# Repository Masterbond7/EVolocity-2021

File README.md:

# EVolocity-2021 Cart Repository

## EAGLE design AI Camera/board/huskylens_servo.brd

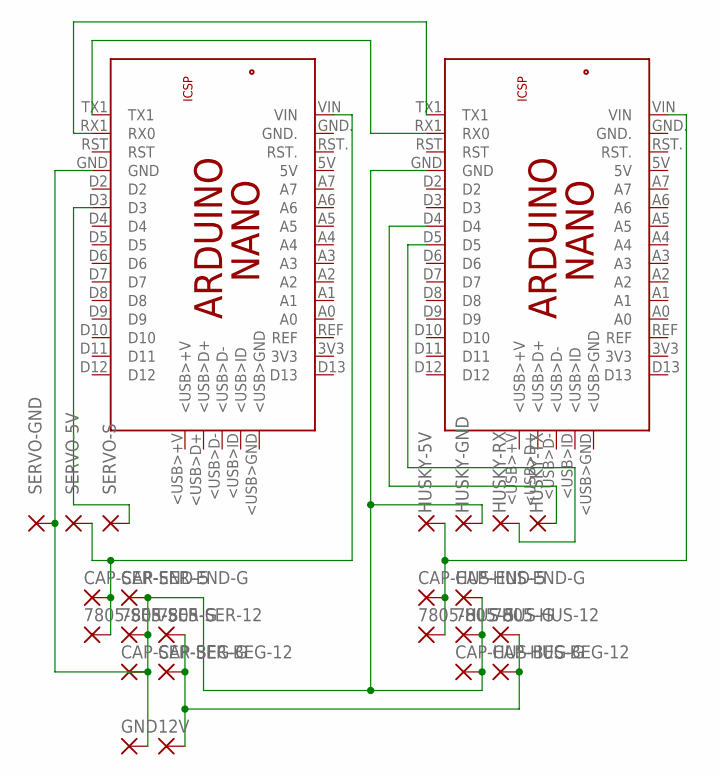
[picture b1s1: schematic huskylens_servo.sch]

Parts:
12V, 7805-HUS-5, 7805-HUS-12, 7805-HUS-G, 7805-SER-5, 7805-SER-12, 7805-SER-G: 2,15/1,0
CAP-HUS-BEG-12: 2,15/1,0
CAP-HUS-BEG-G: 2,15/1,0
CAP-HUS-END-5: 2,15/1,0
CAP-HUS-END-G: 2,15/1,0
CAP-SER-BEG-12: 2,15/1,0
CAP-SER-BEG-G: 2,15/1,0
CAP-SER-END-5: 2,15/1,0
CAP-SER-END-G: 2,15/1,0
GND: 2,15/1,0
HUSKY-5V: 2,15/1,0
HUSKY-ARD: ARDUINO_NANO
HUSKY-GND: 2,15/1,0
HUSKY-RX: 2,15/1,0
HUSKY-TX: 2,15/1,0
SERVO-5V: 2,15/1,0
SERVO-ARD: ARDUINO_NANO
SERVO-GND: 2,15/1,0
SERVO-S: 2,15/1,0

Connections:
unnamed: HUSKY-ARD.RX1 (RX0), SERVO-ARD.TX1
unnamed: HUSKY-ARD.TX1, SERVO-ARD.RX1 (RX0)
unnamed: 7805-HUS-G.1, 7805-SER-G.1, CAP-HUS-BEG-G.1, CAP-HUS-END-G.1, CAP-SER-BEG-G.1, CAP-SER-END-G.1, GND.1, HUSKY-ARD.GND, HUSKY-GND.1, SERVO-ARD.GND, SERVO-GND.1
unnamed: HUSKY-ARD.D5, HUSKY-RX.1
unnamed: SERVO-ARD.D3, SERVO-S.1
unnamed: 12V.1, 7805-HUS-12.1, 7805-SER-12.1, CAP-HUS-BEG-12.1, CAP-SER-BEG-12.1
unnamed: 7805-HUS-5.1, CAP-HUS-END-5.1, HUSKY-5V.1, HUSKY-ARD.VIN
unnamed: 7805-SER-5.1, CAP-SER-END-5.1, SERVO-5V.1, SERVO-ARD.VIN
unnamed: HUSKY-ARD.D4, HUSKY-TX.1

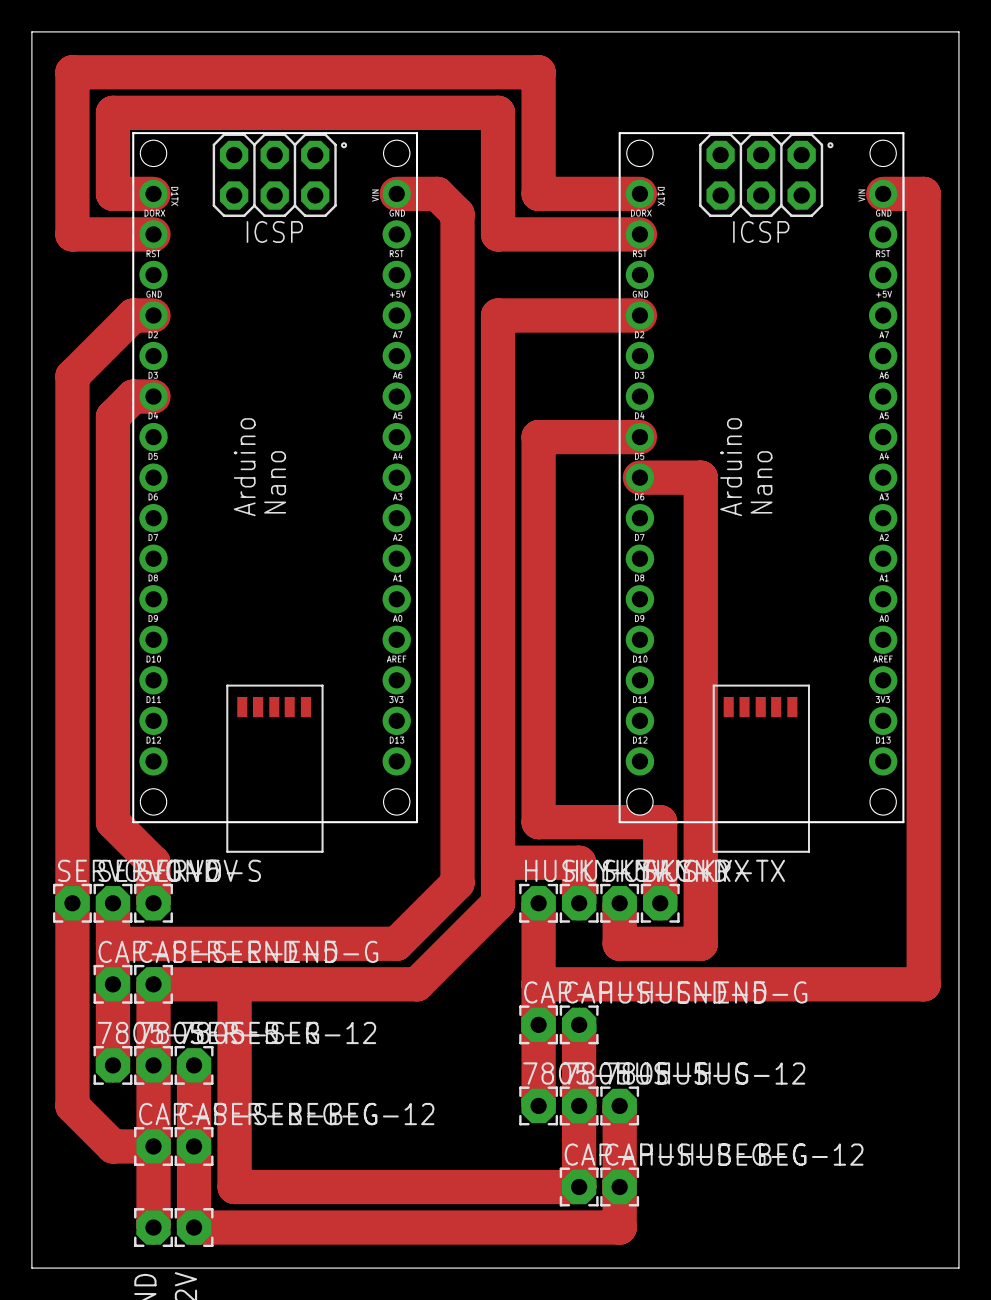
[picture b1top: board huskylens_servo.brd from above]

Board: 2 copper layers, 58.0 x 77.3 mm, 25 parts (0 on the bottom side), 9 nets.

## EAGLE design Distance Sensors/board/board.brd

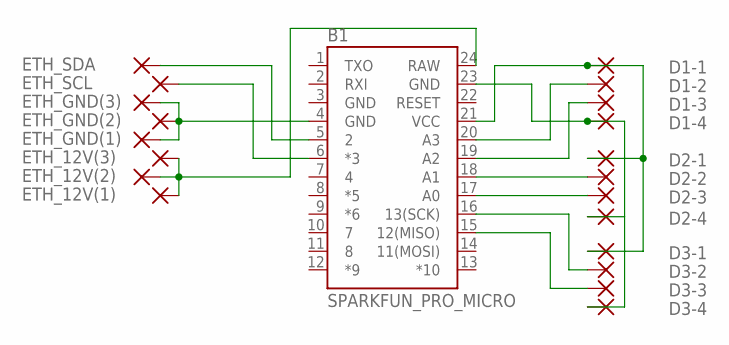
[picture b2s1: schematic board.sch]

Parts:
B1: SPARKFUN_PRO_MICRO
D1-1, D1-2, D1-3, D1-4, D2-1, D2-2, D2-3, D2-4, D3-1, D3-2, D3-3, D3-4: 2,15/1,0
ETH_12V(1), ETH_12V(2), ETH_12V(3): 2,15/1,0
ETH_GND(1), ETH_GND(2), ETH_GND(3): 2,15/1,0
ETH_SCL: 2,15/1,0
ETH_SDA: 2,15/1,0

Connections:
GND: B1.3 (GND)
unnamed: B1.4 (GND), ETH_GND(1).1, ETH_GND(2).1, ETH_GND(3).1
unnamed: B1.23 (GND), D1-4.1, D2-4.1, D3-4.1
unnamed: B1.21 (VCC), D1-1.1, D2-1.1, D3-1.1
unnamed: B1.19 (A2), D1-3.1
unnamed: B1.20 (A3), D1-2.1
unnamed: B1.18 (A1), D2-2.1
unnamed: B1.17 (A0), D2-3.1
unnamed: B1.16 (13(SCK)), D3-2.1
unnamed: B1.15 (12(MISO)), D3-3.1
unnamed: B1.24 (RAW), ETH_12V(1).1, ETH_12V(2).1, ETH_12V(3).1
unnamed: B1.5 (2), ETH_SDA.1
unnamed: B1.6 (*3), ETH_SCL.1

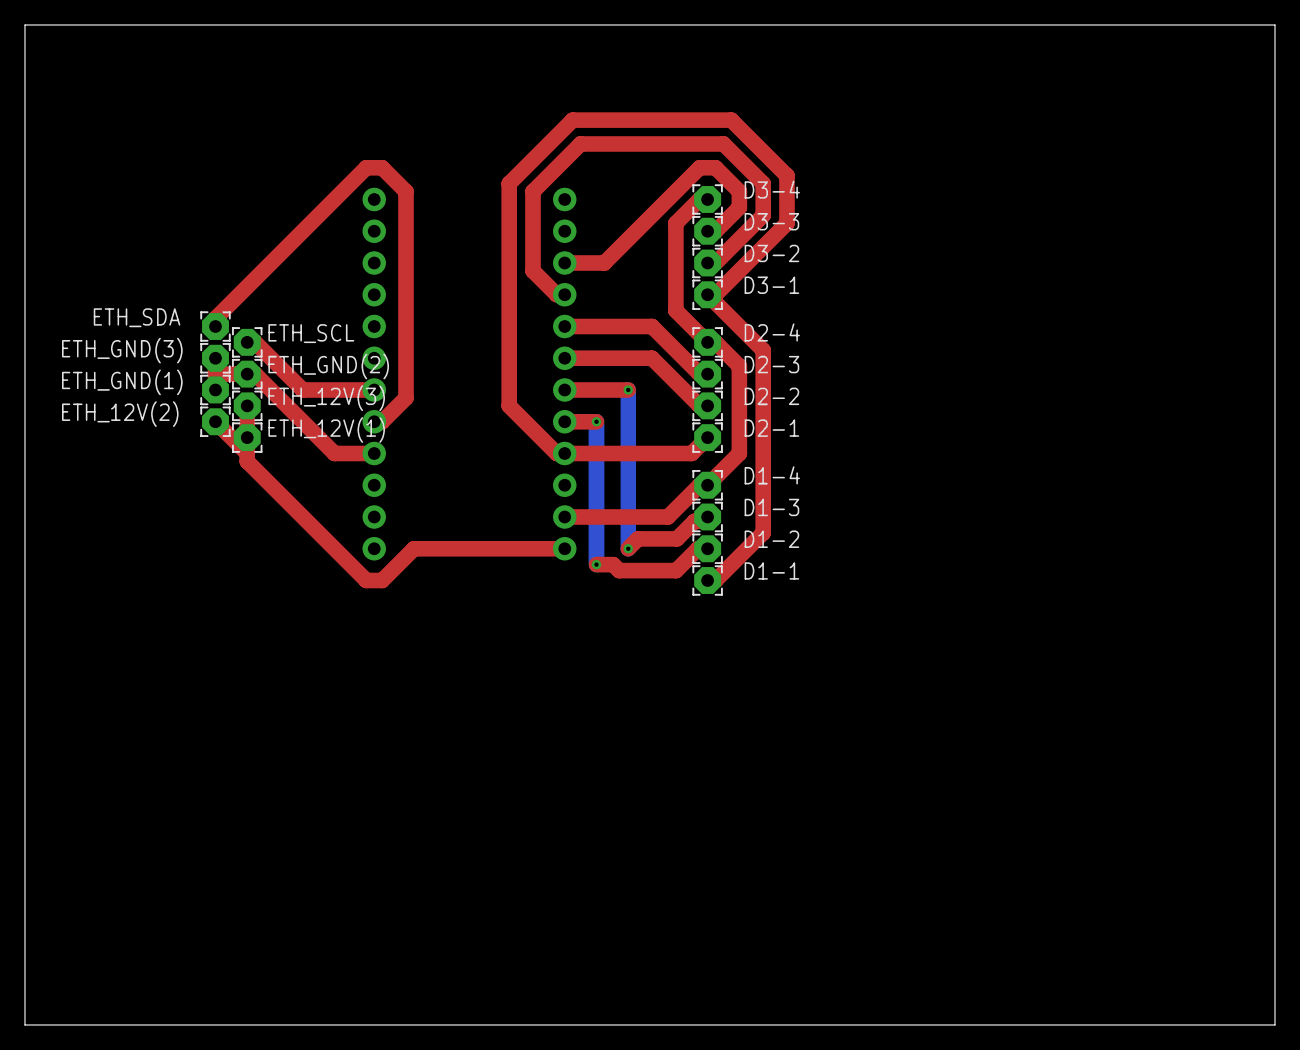
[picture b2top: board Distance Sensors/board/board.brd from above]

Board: 2 copper layers, 100.0 x 80.0 mm, 21 parts (1 on the bottom side), 12 nets.

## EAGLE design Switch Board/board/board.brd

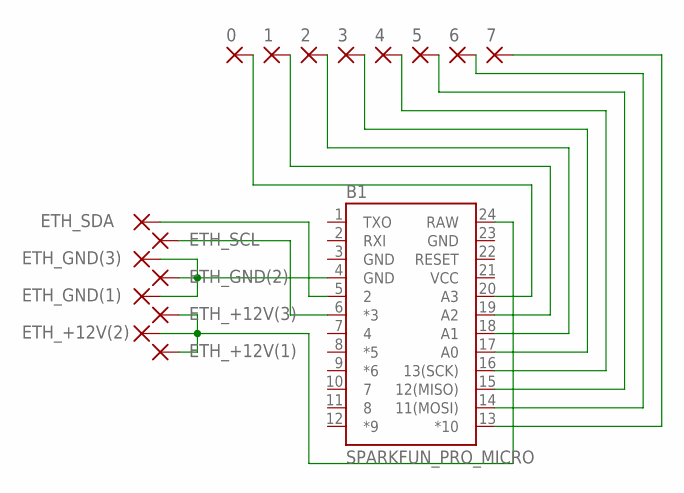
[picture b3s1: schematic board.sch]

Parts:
0, 1, 2, 3, 4, 5, 6, 7: 2,15/1,0
B1: SPARKFUN_PRO_MICRO
ETH_+12V(1), ETH_+12V(2), ETH_+12V(3): 2,15/1,0
ETH_GND(1), ETH_GND(2), ETH_GND(3): 2,15/1,0
ETH_SCL: 2,15/1,0
ETH_SDA: 2,15/1,0

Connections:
GND: B1.3 (GND), B1.23 (GND)
unnamed: B1.5 (2), ETH_SDA.1
unnamed: B1.6 (*3), ETH_SCL.1
unnamed: B1.4 (GND), ETH_GND(1).1, ETH_GND(2).1, ETH_GND(3).1
unnamed: B1.24 (RAW), ETH_+12V(1).1, ETH_+12V(2).1, ETH_+12V(3).1
unnamed: 0.1, B1.20 (A3)
unnamed: 1.1, B1.19 (A2)
unnamed: 2.1, B1.18 (A1)
unnamed: 3.1, B1.17 (A0)
unnamed: 4.1, B1.16 (13(SCK))
unnamed: 5.1, B1.15 (12(MISO))
unnamed: 6.1, B1.14 (11(MOSI))
unnamed: 7.1, B1.13 (*10)
VCC: B1.21 (VCC)

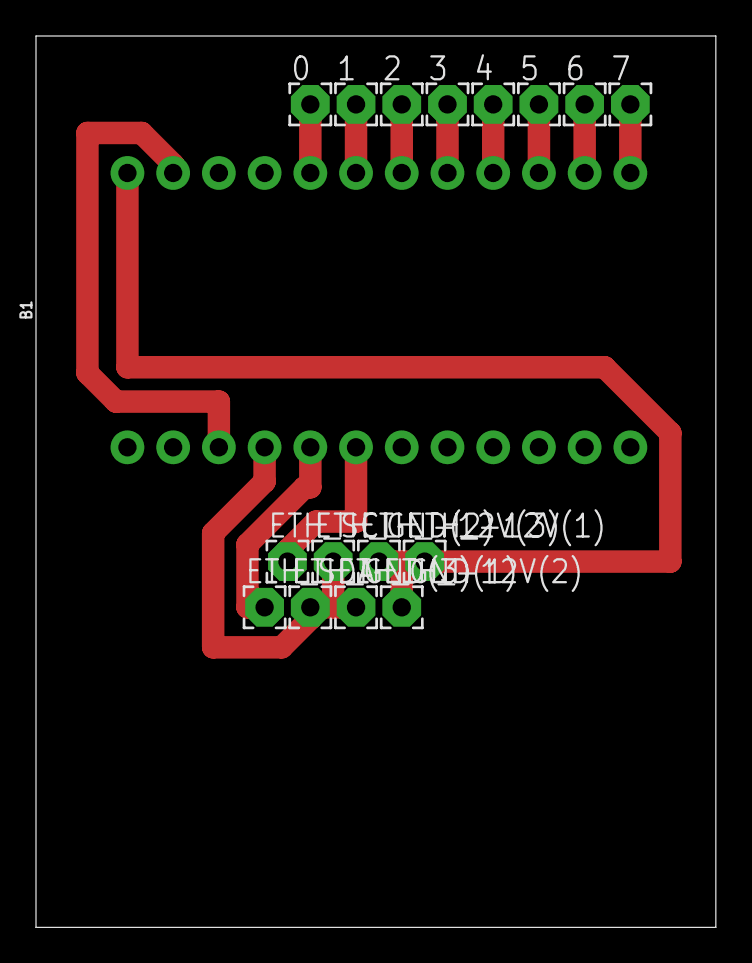
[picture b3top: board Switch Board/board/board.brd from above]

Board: 2 copper layers, 37.8 x 49.5 mm, 17 parts (0 on the bottom side), 13 nets.

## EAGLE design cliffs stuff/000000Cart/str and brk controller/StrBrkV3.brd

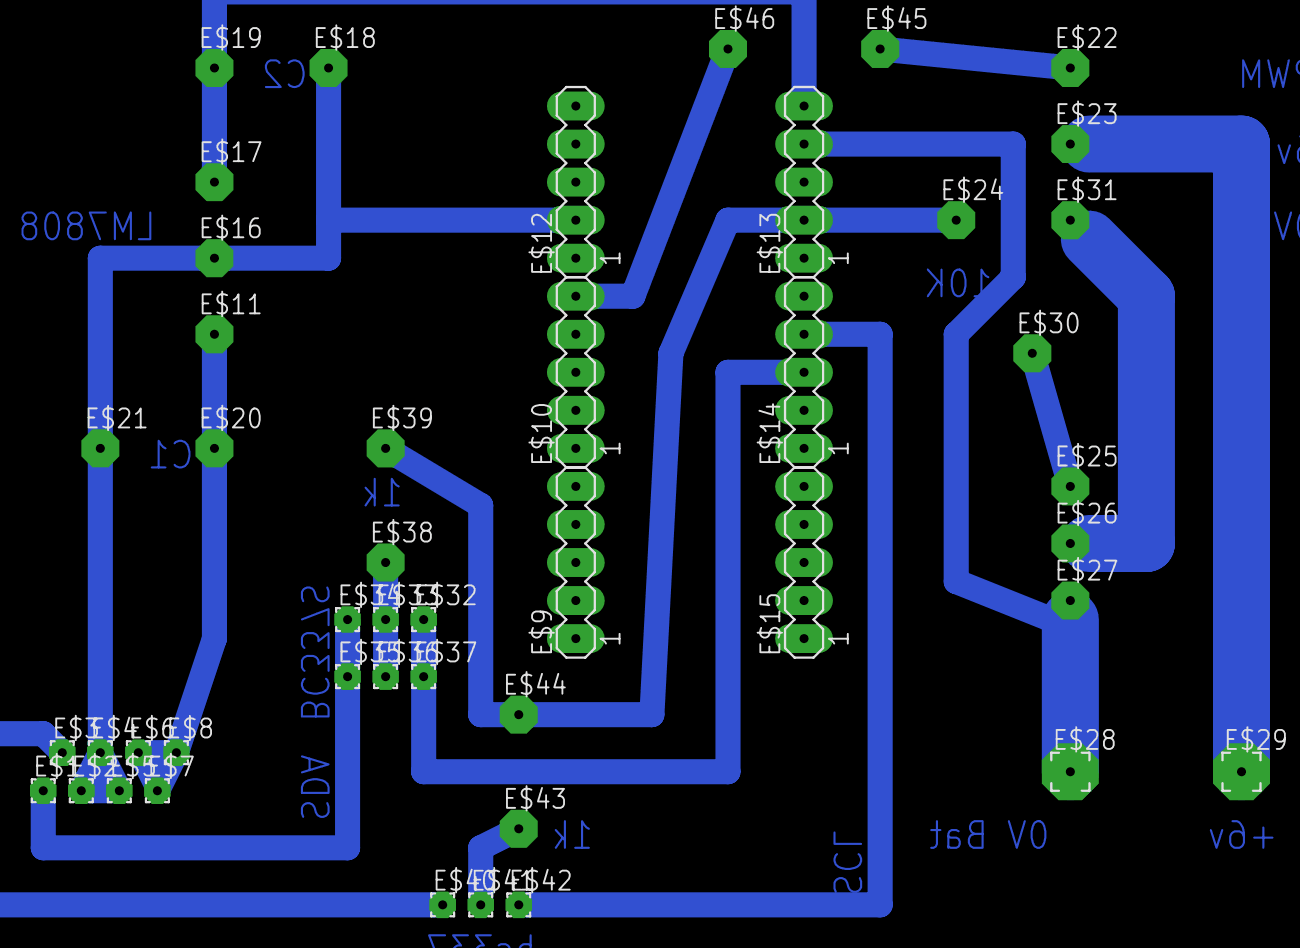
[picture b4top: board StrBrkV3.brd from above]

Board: 2 copper layers, 46 parts (0 on the bottom side), 8 nets.

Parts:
E$1, E$2, E$3, E$4, E$5, E$6, E$7, E$8, E$32, E$33, E$34, E$35, E$36, E$37, E$40, E$41, E$42: 1,6/0,8
E$9, E$10, E$12, E$13, E$14, E$15: MA05-1
E$11, E$16, E$17, E$18, E$19, E$20, E$21, E$22, E$23, E$24, E$25, E$26, E$27, E$30, E$31, E$38, E$39, E$43, E$44, E$45, E$46: 2,15/1,0
E$28, E$29: 2,54/0,8

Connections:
S$1: E$13.5, E$17.1
S$2: E$8.1, E$11.1
S$5: E$24.1, E$39.1
S$6: E$1.1, E$34.1, E$35.1
S$8: E$2.1, E$4.1, E$5.1, E$12.2, E$16.1
S$10: E$14.3, E$32.1, E$37.1
S$11: E$33.1, E$36.1, E$38.1
S$15: E$10.5, E$46.1

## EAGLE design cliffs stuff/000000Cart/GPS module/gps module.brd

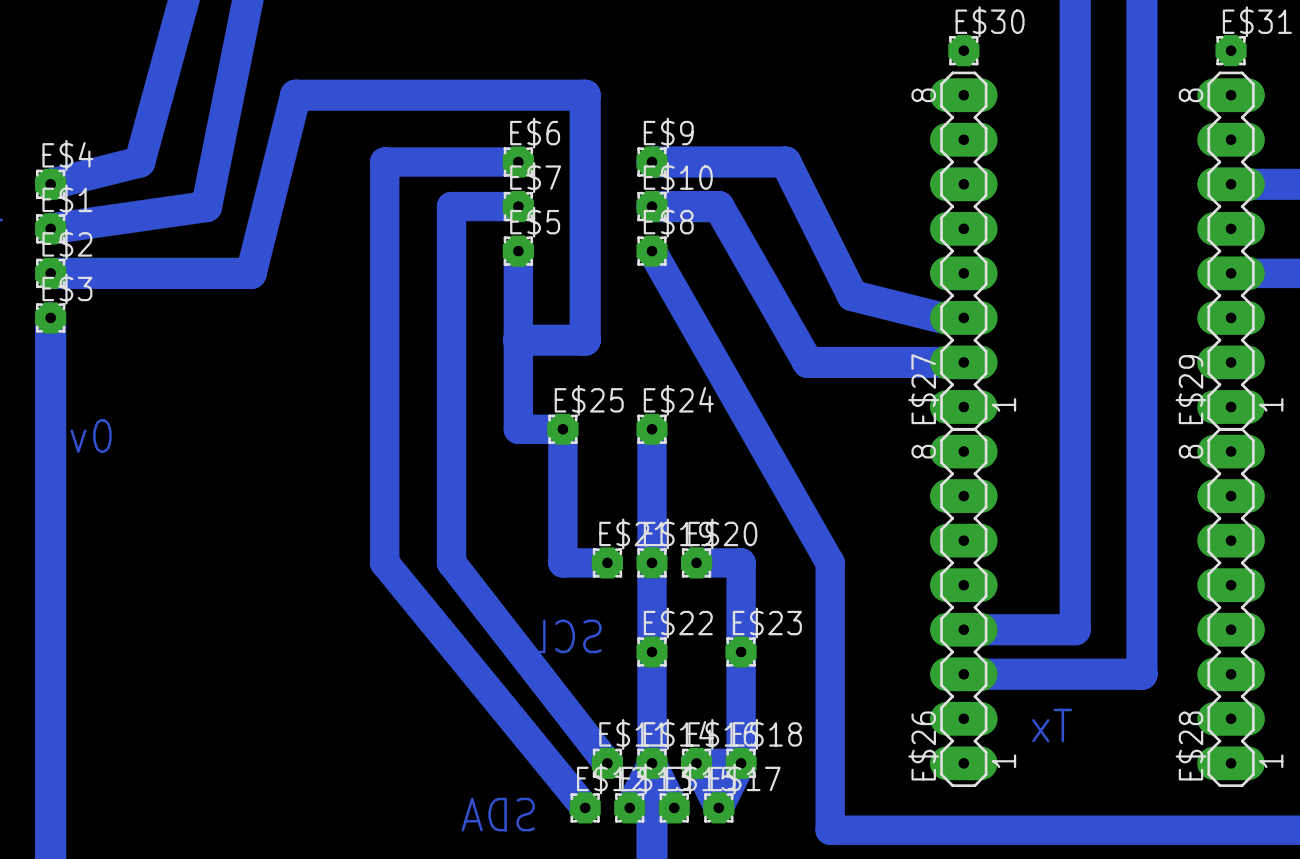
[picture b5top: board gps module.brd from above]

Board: 2 copper layers, 31 parts (0 on the bottom side), 10 nets.

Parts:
E$1, E$2, E$3, E$4, E$5, E$6, E$7, E$8, E$9, E$10, E$11, E$12, E$13, E$14, E$15, E$16, E$17, E$18, E$19, E$20, E$21, E$22, E$23, E$24, E$25, E$30, E$31: 1,6/0,8
E$26, E$27, E$28, E$29: MA08-1

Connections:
S$1: E$7.1, E$11.1
S$2: E$6.1, E$12.1
S$3: E$2.1, E$5.1, E$21.1, E$25.1
S$4: E$13.1, E$14.1, E$15.1, E$19.1, E$22.1, E$24.1
S$5: E$3.1, E$29.6
S$6: E$8.1, E$29.4
S$7: E$10.1, E$27.2
S$9: E$16.1, E$17.1, E$18.1, E$20.1
S$10: E$1.1, E$26.4
S$11: E$4.1, E$26.3

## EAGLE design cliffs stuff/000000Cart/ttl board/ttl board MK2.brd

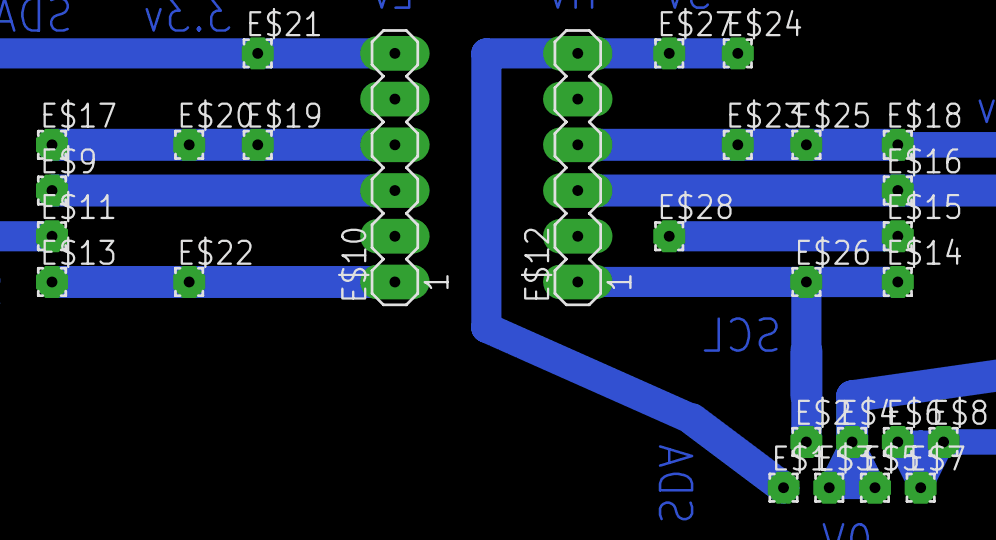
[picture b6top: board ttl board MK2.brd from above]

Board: 2 copper layers, 28 parts (0 on the bottom side), 8 nets.

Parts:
E$1, E$2, E$3, E$4, E$5, E$6, E$7, E$8, E$9, E$11, E$13, E$14, E$15, E$16, E$17, E$18, E$19, E$20, E$21, E$22, E$23, E$24, E$25, E$26, E$27, E$28: 1,6/0,8
E$10, E$12: MA06-1

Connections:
S$1: E$6.1, E$7.1, E$8.1, E$12.4, E$18.1
S$2: E$2.1, E$12.1, E$14.1, E$26.1
S$3: E$10.4, E$17.1
S$4: E$3.1, E$4.1, E$5.1, E$12.3, E$16.1
S$5: E$9.1, E$10.3
S$6: E$10.6, E$11.1, E$21.1
S$7: E$10.1, E$13.1
S$9: E$1.1, E$12.6, E$24.1

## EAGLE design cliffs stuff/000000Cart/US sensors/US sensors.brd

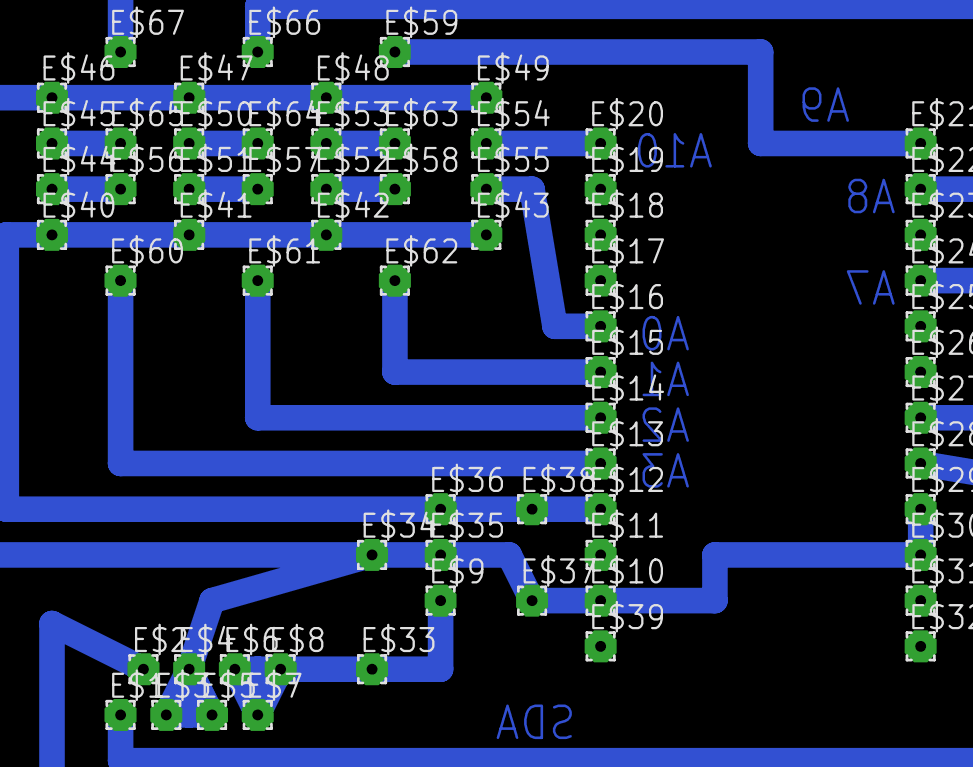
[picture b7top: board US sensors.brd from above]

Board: 2 copper layers, 67 parts (0 on the bottom side), 18 nets.

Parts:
E$1, E$2, E$3, E$4, E$5, E$6, E$7, E$8, E$9, E$10, E$11, E$12, E$13, E$14, E$15, E$16, E$17, E$18, E$19, E$20, E$21, E$22, E$23, E$24, E$25, E$26, E$27, E$28, E$29, E$30, E$31, E$32, E$33, E$34, E$35, E$36, E$37, E$38, E$39, E$40, E$41, E$42, E$43, E$44, E$45, E$46, E$47, E$48, E$49, E$50, E$51, E$52, E$53, E$54, E$55, E$56, E$57, E$58, E$59, E$60, E$61, E$62, E$63, E$64, E$65, E$66, E$67: 1,6/0,8

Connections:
S$1: E$3.1, E$4.1, E$5.1, E$10.1, E$29.1, E$30.1, E$35.1, E$46.1, E$49.1
S$2: E$13.1, E$60.1
S$3: E$6.1, E$7.1, E$8.1, E$9.1
S$4: E$1.1, E$28.1
S$5: E$2.1, E$27.1
S$6: E$12.1, E$36.1, E$38.1, E$43.1
S$7: E$44.1, E$56.1
S$8: E$51.1, E$57.1
S$9: E$52.1, E$58.1
S$11: E$14.1, E$61.1
S$12: E$15.1, E$62.1
S$13: E$20.1, E$54.1
S$15: E$53.1, E$63.1
S$16: E$22.1, E$66.1
S$17: E$24.1, E$67.1
S$18: E$50.1, E$64.1
S$19: E$45.1, E$65.1
S$20: E$16.1, E$55.1

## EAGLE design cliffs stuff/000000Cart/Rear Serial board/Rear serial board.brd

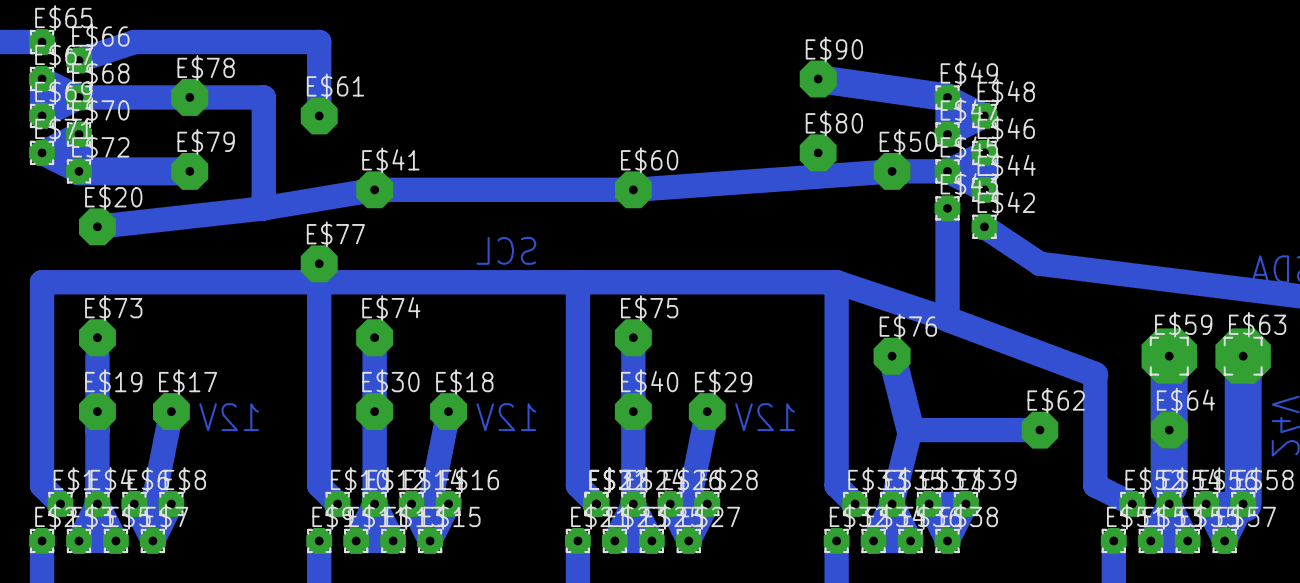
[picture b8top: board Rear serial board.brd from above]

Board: 2 copper layers, 81 parts (0 on the bottom side), 16 nets.

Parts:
E$1, E$2, E$3, E$4, E$5, E$6, E$7, E$8, E$9, E$10, E$11, E$12, E$13, E$14, E$15, E$16, E$21, E$22, E$23, E$24, E$25, E$26, E$27, E$28, E$31, E$32, E$33, E$34, E$35, E$36, E$37, E$38, E$39, E$42, E$43, E$44, E$45, E$46, E$47, E$48, E$49, E$51, E$52, E$53, E$54, E$55, E$56, E$57, E$58, E$65, E$66, E$67, E$68, E$69, E$70, E$71, E$72: 1,6/0,8
E$17, E$18, E$19, E$20, E$29, E$30, E$40, E$41, E$50, E$60, E$61, E$62, E$64, E$73, E$74, E$75, E$76, E$77, E$78, E$79, E$80, E$90: 2,15/1,0
E$59, E$63: 2,54/0,8

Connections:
S$2: E$6.1, E$7.1, E$8.1, E$17.1
S$3: E$14.1, E$15.1, E$16.1, E$18.1
S$4: E$11.1, E$12.1, E$13.1, E$30.1, E$74.1
S$5: E$23.1, E$24.1, E$25.1, E$40.1, E$75.1
S$6: E$70.1, E$71.1, E$72.1
S$7: E$37.1, E$38.1, E$39.1
S$8: E$56.1, E$57.1, E$58.1, E$63.1
S$9: E$53.1, E$54.1, E$55.1
S$10: E$47.1, E$48.1, E$49.1, E$90.1
S$11: E$20.1, E$41.1, E$44.1, E$45.1, E$46.1, E$50.1, E$60.1, E$67.1, E$68.1, E$69.1
S$12: E$26.1, E$27.1, E$28.1, E$29.1
S$13: E$1.1, E$10.1, E$22.1, E$33.1, E$43.1, E$52.1
S$15: E$3.1, E$4.1, E$5.1, E$19.1
S$16: E$34.1, E$35.1, E$36.1, E$62.1, E$76.1
S$18: E$61.1, E$66.1
S$21: E$2.1, E$9.1, E$21.1, E$32.1, E$42.1, E$51.1, E$65.1

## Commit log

2021-01-06 Updating README.md
2021-01-08 Adding the basic plans for the 2021 cart
2021-01-08 Updating cart plans
2021-01-09 Extra changes to plan
2021-01-09 Created cart checklist
2021-01-09 Added folders and updated cart checklist
2021-01-09 Deleted blank text files
2021-01-09 Adding blank code files and folders for organisation
2021-01-09 __pycache__
2021-01-10 Added PRE-ELECTRONICS data gathering and storage for the Raspberry PI
2021-01-10 Added PRE-ELECTRONICS data storage on the local directory
2021-01-11 Added JSON module in dependencies folder, also added code to notify gearbox of mode change (gets mode data from JSON file)
2021-01-11 Adding the ability to foward data from the user to the movement controller
2021-01-12 .pyc files
2021-01-12 Added opencv and flask + their dependencies to the dependencies folder and made a new branch for testing the raspberry pi's website
2021-01-12 Long term data storage
2021-01-12 moving dependencies
2021-01-12 removing dependencies folder(doesn't work as intended might add back later)
2021-01-12 fixing imports
2021-01-12 added dependencies.txt
2021-01-12 fixed typo in imports
2021-01-12 Removed dependencies folder from main branch
2021-01-12 reversing small change
2021-01-13 starting to add pygame
2021-01-13 Live website testing (basic camera)
2021-01-14 Added live text to the website using the htmx library (thanks to u/01binary)
2021-01-14 i did some things, like pretty pictures and things that go wee
2021-01-14 Test image loads once but does not get reloaded yet
2021-01-14 added icons for when the car enivitibley explodes or sets ablaze. oh and a map but it doesn't work yet because we have no money
2021-01-15 Placeholder map image can be updated live on the website
2021-01-20 Embedded live(ish) google map reading from seperate file + Dark theme for website + Imporved data saving to the save_data.txt file.
2021-01-20 Merging the Website Testing file with the Main code file
2021-01-20 fixed the tick mark in cart checklist.txt
2021-01-21 Removed debug GPS variables at the bottom of the page.
2021-01-21 Removed the need for save_data.txt and removed the bug where text would occasionally not load on the website due to the file being written to by another thread, also added a mode override fow when yo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
2021-01-21 Fixed a bug found by Joe where the console doesn't support float support as input
2021-01-22 Added most of second hud and the ability to switch between them via button press. This will be finalised as tapping anywhere on the screen
2021-01-24 minor clean up, leaving the rest for james
2021-01-24 Cleaning up max's code in preparation for the merge with the main branch
2021-01-24 Merging main branch into hud branch and adding a seperate folder for images
2021-01-24 Merged code from max's HUD testing with my website code for the Raspberry PI
2021-01-24 Updating cart checklist file
2021-01-24 Hopefully fixed a bug where Tkinter was being unhappy and causing core dumps left right and center because it was being entitled and wants to be ran in the main thread
2021-01-24 Fixed where the detailed hud gets some of its variables from
2021-01-24 Got all of the features intended to work in this update to work in this update
2021-01-24 Little bit of code cleaning + got arduino command interpreter to actually interperet the battery voltage variable
2021-01-25 Made board and schematic for the AI Camera circut
2021-01-25 Added the AI Camera to a new section of the cart checklist for the steps of making the PCBs
2021-01-25 More woek on the AI Camera PCB
2021-01-29 Finished (hopefully for now) adding pcb specs to the cart checklist file
2021-01-30 started design work on custom boards for the car
2021-01-30 Wired up max's board with autorouter
2021-01-30 ACTUALLY wired up max's board
2021-01-30 removed irrelevant board files
2021-01-30 Updated cart checklist and created printable copy of the board
2021-01-30 added the rest of the variables for the detailed hud and a minor cosmetic change
2021-02-06 Started on the schematic (just need to add the voltage sensing stuff now)
2021-02-06 designed distance sensor board and sending to james for autorouting
2021-02-06 Routing board (2 VIAS)
2021-02-06 cleaned up excess files
2021-03-14 Adding a file for testing code for the gps module
2021-03-25 Updating Prerequisites
2021-03-31 Adding the thing to measure voltages
2021-05-27 Fixed the code to display the images using Tk for linux
2021-06-27 Added some items onto the checklist for things that need to be done soon in the workshop.
2021-08-22 Added the code for the husky lens and the servo arduinos
2021-08-29 Adding cliffs files
2021-08-29 Added 3D Models folder and code for user inputs???
2021-09-01 updated gearbox controller
2021-09-08 Adde code for the steering wheel
2021-09-08 Fixed the code for the arduino as pins A6 and A7 cannot be read as digital pins on our nanos
2021-09-23 Changed code.py so it ran on the raspberry pi
2021-09-23 test code to move the steering servo
2021-09-27 Added code to the steering wheel for I2C
2021-11-17 added python i2c
2021-11-18 Got the steering wheel to move the wheels
2021-11-18 Edited steering wheel code and servo code
2021-11-24 Added steering stress test and made steering faster
2021-11-24 Edited the stress test program for the improved servo performance
2021-11-24 I2C for pedals
2021-11-24 Raspberry pi reading pedals
2021-11-24 Made the arduino actually send data this time
2021-12-02 Breakes
2022-01-18 Added 4 us sensors code
2022-01-24 Added code to the brake servo controller code so that the last angle transmitted gets constantly sent
2022-01-24 Unlocked the secrets of the universe
2022-01-27 Manual pwm code and actually good brakes and manual servo controll
2022-01-28 Made the steering better
2022-03-16 V8 sound effect test
2022-03-16 Fixed raspberry pi not playing by changing from the playsound module to pydub
2022-03-16 Sound effect now stops when accelerator is pressed
2022-03-16 Fixed syntax error
2022-03-16 Added deadzone for sound stopping
2022-03-17 Found a much better solution to stopping the sound effect
2022-03-17 Removed the copy of pi2c.py
2022-03-17 Fixed up a comment
2022-03-17 Created maybe temporary try except statement to fix errors
2022-03-17 Fixed the try except
2022-03-17 Stoopid indentation based language
2022-03-17 Removed if poll is None because it might the the cause of my confusion
2022-03-17 Changed some try except staments around for bug testing
2022-03-17 More bug testing
2022-03-17 And more
2022-03-17 More
2022-03-17 Created test file because thing aren't going to plan
2022-03-17 Die already
2022-03-17 WHY WONT YOU DIE?
2022-03-17 i think its working
2022-03-17 Created another test program
2022-03-17 Cmon work already
2022-03-17 I believe it works!
2022-03-18 Testing if the issues are due to the proccess being called multiple times
2022-03-18 Simpler test of the previous
2022-03-18 Oh yeah! Things are working. Removed test code
2022-03-18 Stopped showing the progress of the audio
2022-03-22 Brakes now accelerator
2022-03-22 Reversed direction of the servo
2022-04-03 Brakes are now brakes again
2022-04-03 Relocating the engine sound effect code
2022-04-03 Steering angle -= 1
2022-04-03 maybe prevent steering crashing
    it really shouldn't have previously though
2022-04-03 Almost finished rewriting ultrasonics code
2022-04-03 Fixed the semi-broken new code
2022-04-13 Fixed up some of the hud code
2022-05-18 Added extra if statement to only send data to the steering servo if the value is between 0 and 180 (inclusive)
2022-05-18 changed the if statement in the steering servo controller to modify instead of change back if invalid angle is given
2022-05-20 sdgvsdvg
2022-09-21 Added code for new steering board and changed steering wheel to serial
2022-09-22 Created code to move the gearbox, and read the hall effect sensor
2022-09-22 removed non-steering bytes from being sent
2022-09-22 Changed the code so it reads the steering position directly from the potentiometer
2022-09-22 fixed missing bracker
2022-09-24 Gearbox code changes
2022-09-24 Futher gearbox code changes, should read rpm more accurately
2022-10-30 Str brk controller and playing mp3 from sd card arduino
2022-11-01 idk what happened in this change, past me is a nonce
2022-11-01 Rewrote the program to utilize an interrupt pin (besides the old one was horrendous)
2022-11-01 Fixed a few things
2022-11-01 Spacing
2022-11-01 Missed a space
2022-11-01 Changed gearbox code to work a bit more and also sd card mp3 player
2022-11-02 Fixed code reading RPM like a sawtooth wave
2022-11-02 Code should now be ready for an irl real test
2022-11-02 tab instead of space for niceness
2022-11-02 made shifting more effiecent
2022-11-03 Added program for paddle shifting
2022-11-03 Oops, didn't actualy change the file
2022-11-03 wtf arduino ide
2022-11-03 elif isn't an arduino thing me
2022-11-03 evOlocity not evElocity idiot
2022-11-03 stopped paddles shifting when they shouldn't
2022-11-03 Created program to find total steps between the limit switches
2022-11-03 Changed titles
2022-11-06 Added brake servo controller code

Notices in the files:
parts and their libraries:
SparkFun-Boards: Licensing: Creative Commons ShareAlike 4.0 International - https://creativecommons.org/licenses/by-sa/4.0
